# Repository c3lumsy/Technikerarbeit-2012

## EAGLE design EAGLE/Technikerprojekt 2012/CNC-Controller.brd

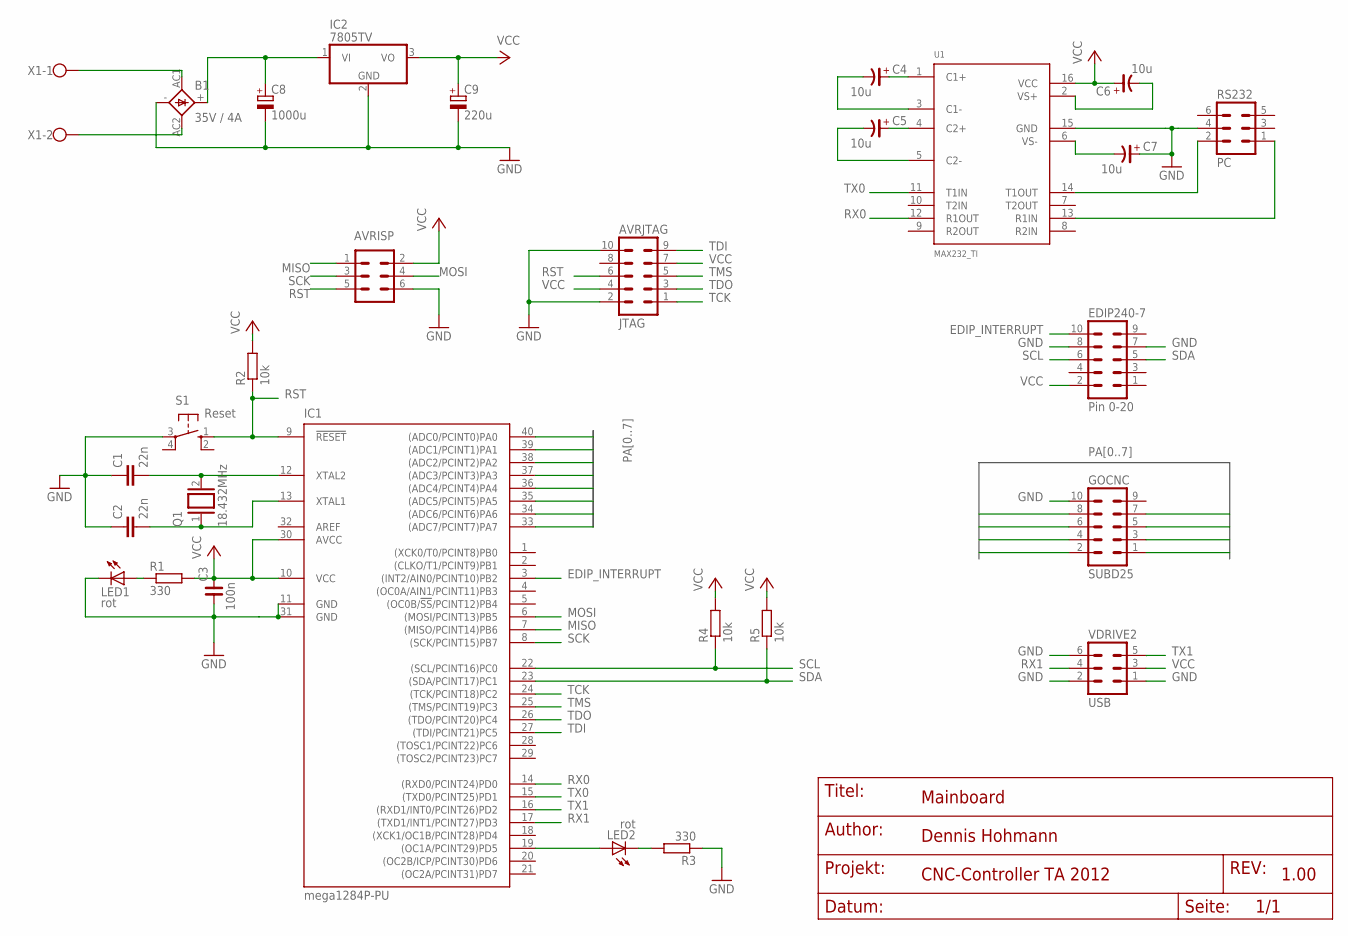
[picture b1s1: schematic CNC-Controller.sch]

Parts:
AVRISP: ISP; ML6
AVRJTAG: JTAG; ML10
B1: 35V / 4A; KBU
C1, C2: 22n; C025-025X050
C3: 100n; C025-050X025
C4, C5, C6, C7: 10u; CTT-025-050
C8: 1000u; E5-13
C9: 220u; E2-5
EDIP240-7: Pin 0-20; ML10
GOCNC: SUBD25; ML10
IC1: mega1284P-PU; DIL40
IC2: 7805TV; TO220V
LED1, LED2: rot; LED3MM
Q1: 18.432MHz; QS
R1, R3: 330; 0207/10
R2, R4, R5: 10k; 0207/10
RS232: PC; ML6
S1: Reset; B3F-10XX
U1: MAX232_TI; DIL16
VDRIVE2: USB; ML6
X1: W237-102

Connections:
AREF: IC1.32 (AREF)
EDIP_INTERRUPT: EDIP240-7.10, IC1.3 ((INT2/AIN0/PCINT10)PB2)
GND: AVRISP.6, AVRJTAG.2, AVRJTAG.10, B1.-, C1.1, C2.1, C3.1, C7.+, C8.-, C9.-, EDIP240-7.7, EDIP240-7.8, GOCNC.10, IC1.11 (GND), IC1.31 (GND), IC2.2 (GND), LED1.K (C), R3.1, RS232.4, S1.3, U1.15 (GND), VDRIVE2.1, VDRIVE2.2, VDRIVE2.6
MISO: AVRISP.1, IC1.7 ((MISO/PCINT14)PB6)
MOSI: AVRISP.4, IC1.6 ((MOSI/PCINT13)PB5)
unnamed: C1.2, IC1.12 (XTAL2), Q1.2
unnamed: C4.+, U1.1 (C1+)
unnamed: LED1.A, R1.1
unnamed: C4.-, U1.3 (C1-)
unnamed: C2.2, IC1.13 (XTAL1), Q1.1
unnamed: C5.+, U1.4 (C2+)
unnamed: C5.-, U1.5 (C2-)
unnamed: C6.-, U1.2 (VS+)
unnamed: RS232.2, U1.14 (T1OUT)
unnamed: RS232.1, U1.13 (R1IN)
unnamed: C7.-, U1.6 (VS-)
unnamed: IC1.19 ((OC1A/PCINT29)PD5), LED2.A
unnamed: LED2.K (C), R3.2
PA0: GOCNC.1, IC1.40 ((ADC0/PCINT0)PA0)
PA1: GOCNC.2, IC1.39 ((ADC1/PCINT1)PA1)
PA2: GOCNC.3, IC1.38 ((ADC2/PCINT2)PA2)
PA3: GOCNC.4, IC1.37 ((ADC3/PCINT3)PA3)
PA4: GOCNC.5, IC1.36 ((ADC4/PCINT4)PA4)
PA5: GOCNC.6, IC1.35 ((ADC5/PCINT5)PA5)
PA6: GOCNC.7, IC1.34 ((ADC6/PCINT6)PA6)
PA7: GOCNC.8, IC1.33 ((ADC7/PCINT7)PA7)
RST: AVRISP.5, AVRJTAG.6, IC1.9 (!RESET), R2.1, S1.1 (S)
RX0: IC1.14 ((RXD0/PCINT24)PD0), U1.12 (R1OUT)
RX1: IC1.17 ((TXD1/INT1/PCINT27)PD3), VDRIVE2.4
SCK: AVRISP.3, IC1.8 ((SCK/PCINT15)PB7)
SCL: EDIP240-7.6, IC1.22 ((SCL/PCINT16)PC0), R4.1
SDA: EDIP240-7.5, IC1.23 ((SDA/PCINT17)PC1), R5.1
TCK: AVRJTAG.1, IC1.24 ((TCK/PCINT18)PC2)
TDI: AVRJTAG.9, IC1.27 ((TDI/PCINT21)PC5)
TDO: AVRJTAG.3, IC1.26 ((TDO/PCINT20)PC4)
TMS: AVRJTAG.5, IC1.25 ((TMS/PCINT19)PC3)
TX0: IC1.15 ((TXD0/PCINT25)PD1), U1.11 (T1IN)
TX1: IC1.16 ((RXD1/INT0/PCINT26)PD2), VDRIVE2.5
U+: B1.+, C8.+, IC2.1 (VI)
UB+: B1.AC1, X1.1
UB-: B1.AC2, X1.2
VCC: AVRISP.2, AVRJTAG.4, AVRJTAG.7, C3.2, C6.+, C9.+, EDIP240-7.2, IC1.10 (VCC), IC1.30 (AVCC), IC2.3 (VO), R1.2, R2.2, R4.2, R5.2, U1.16 (VCC), VDRIVE2.3

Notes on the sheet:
Dennis Hohmann
Mainboard
1.00
CNC-Controller TA 2012

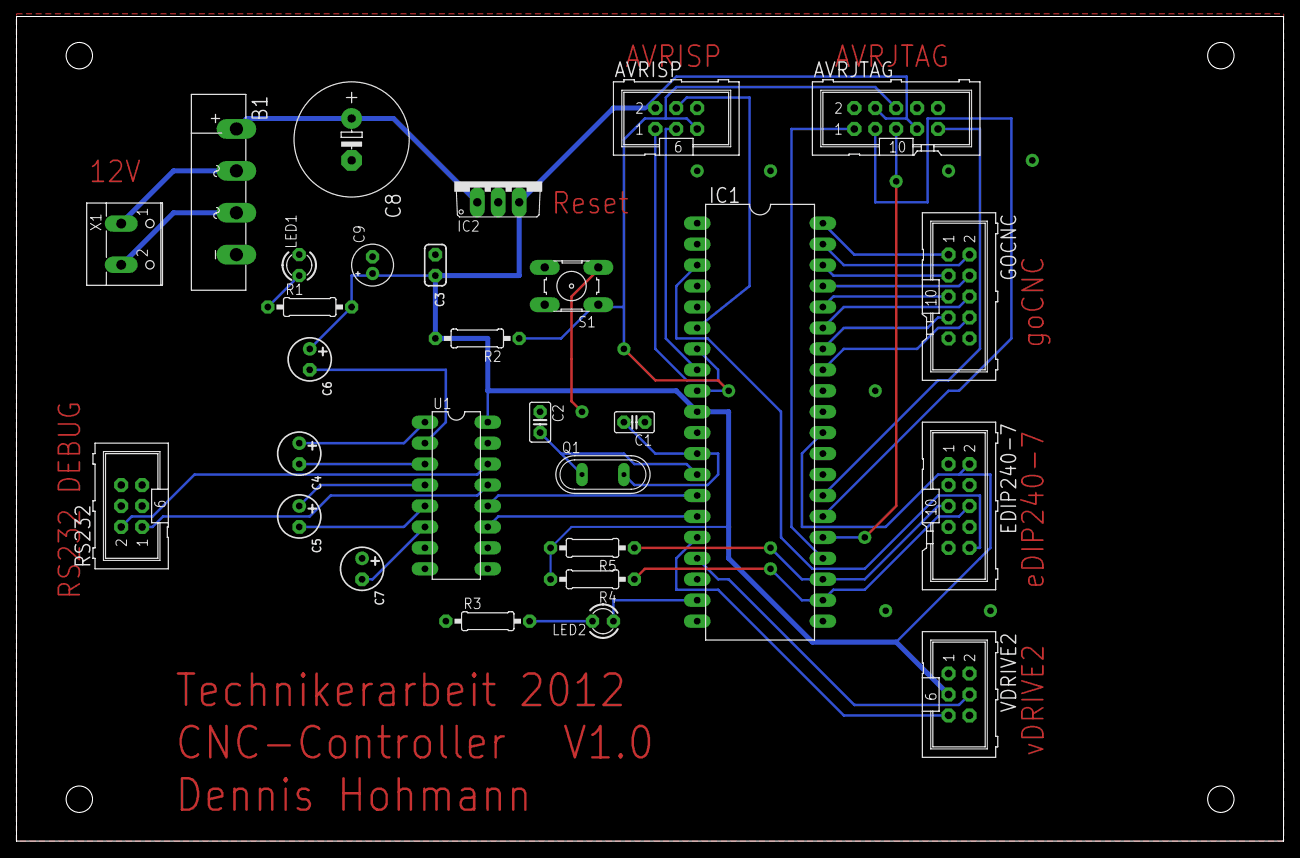
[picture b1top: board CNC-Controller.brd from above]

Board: 2 copper layers, 153.7 x 100.0 mm, 29 parts (0 on the bottom side), 41 nets.

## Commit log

2011-11-14 First add
2011-11-16 goCNC first run!
2011-11-20 gocnc
2011-11-23 Update Header, "non-float", um-scale
2011-11-28 non-float, bresenham line impl. _delay() in step() fixing"
2011-11-28 16bit abs() bug, bresenham bug
2011-11-29 abs() to labs() fix, Bresenham-fix
2011-12-04 "struct" impl.
    axis_step, axis_move, axis_move_parallel, axis_move_interpol changed to
    struct_axis
2011-12-05 axis_move_parallel & _interpol +/- fix
2011-12-18 uart1_gets, vnc1l impl
2012-01-09 gocnc AxisRelPos fix, global temp int32_t i2c impl
2012-02-05 EA eDIP240-7 Application
2012-02-06 I2C fix
2012-02-16 EAGLE & Display UPDATE
    EAGLE: create Schematic
    Display: create Menue-Strukt
2012-02-17 Doku and Schematic UPDATE
2012-02-17 Schematic UPDATE
2012-02-23 code cleaning, display update
2012-02-26 bug !edip_put_POS!
2012-02-26 cleaning!
2012-04-01 final SW version
2012-04-01 Docu update
2012-04-15 Docu update, Docu-CD update
2012-04-15 FINAL RELEASE
2012-06-22 FINAL
    Final Docu & Präsentation
